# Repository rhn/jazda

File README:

Jazda is a bicycle computer based on AVR microcontrollers and mobile phone screens. The project covers both the software and hardware design, providing the source code and schematics.
Originally, it was built around AtTiny2313, now it's AtMega8. The microcontrollers were chosen because of their popularity and resistance to damage.
The other significant component is the screen. The project aims to be compatible with at least a few popular low-powered displays in the future, but at the moment only one is supported.

Project page:
https://github.com/rhn/jazda
Project wiki:
https://github.com/rhn/jazda/wiki/
Introduction, tutorial and hardware documents:
http://rhn.github.com/jazda/

FEATURES

5 speed measuring functions: current, max, average etc
Cadence measurement
Plotting as you ride
Low power consumption
DIY hardware
Modular code design

ASSEMBLY

For hardware needed to assemble the device, see docs/hardware
The schematics are available in Eagle format in eagle directory AND on the
project page (PNG format).
You will need an AVR programmer to upload the software to the chip!

SOFTWARE BUILDING

Linux:
To build & upload the software, you need:
- avr-gcc
- avr-libc
- avrdude
- Unix shell
1. Connect the AtMega8 chip to your computer using
your programmer (refer to the programmer's manual)
2. Consult avrdude manual to find your programmer's name (in this example, it's
"usbasp")
2. Issue the commands:
cd src
sh ../build.sh usbasp m8 main.c
replacing "usbasp" with your programmer's name

AUTHORS
rhn@porcupinefactory.org

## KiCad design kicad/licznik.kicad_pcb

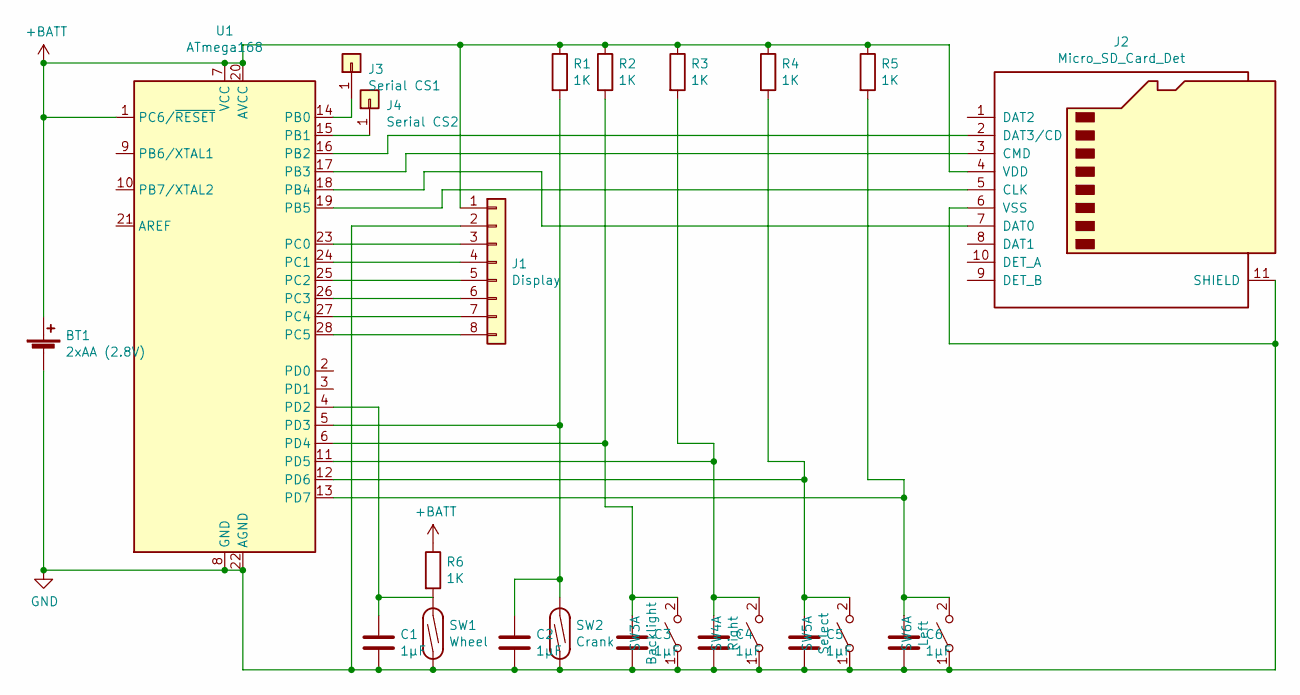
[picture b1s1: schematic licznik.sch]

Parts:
BT1: 2xAA (2.8V); PinHeader_1x02_P2.54mm_Vertical
C1, C2, C3: 1µF; C_0805_2012Metric_Pad1.15x1.40mm_HandSolder
C4, C5, C6: 1µF; C_0805_2012Metric
J1: Display; Nokia screen
J2: Micro_SD_Card_Det; SD_pins
J3: Serial CS1; PinHeader_1x01_P2.54mm_Horizontal
J4: Serial CS2; PinHeader_1x01_P2.54mm_Horizontal
R1, R2, R3, R4, R5, R6: 1K; R_0603_1608Metric
SW1: Wheel; PinHeader_1x02_P2.54mm_Horizontal
SW2: Crank; PinHeader_1x02_P2.54mm_Horizontal
SW3: Backlight; SW_PUSH_6mm_H5mm
SW4: Right; SW_PUSH_6mm_H5mm
SW5: Select; SW_PUSH_6mm_H5mm
SW6: Left; SW_PUSH_6mm_H5mm
U1: ATmega168; DIP-28_W7.62mm

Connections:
+BATT: BT1.1 (+), J1.1, J2.4 (VDD), R1.1, R2.1, R3.1, R4.1, R5.1, R6.1, U1.1 (PC6/~RESET), U1.7 (VCC), U1.20 (AVCC); also elsewhere on the board
GND: BT1.2 (-), C1.2, C2.2, C3.2, C4.2, C5.2, C6.2, J1.2, J2.6 (VSS), J2.11 (SHIELD), SW1.1, SW2.1, SW3.1, SW4.1, SW5.1, SW6.1, U1.8 (GND), U1.22 (AGND); also elsewhere on the board
unnamed: C1.1, R6.2, SW1.2, U1.4 (PD2)
unnamed: C2.1, R1.2, SW2.2, U1.5 (PD3)
unnamed: C3.1, R2.2, SW3.2, U1.6 (PD4)
unnamed: C4.1, R3.2, SW4.2, U1.11 (PD5)
unnamed: C5.1, R4.2, SW5.2, U1.12 (PD6)
unnamed: C6.1, R5.2, SW6.2, U1.13 (PD7)
unnamed: J1.3, U1.23 (PC0)
unnamed: J1.4, U1.24 (PC1)
unnamed: J1.5, U1.25 (PC2)
unnamed: J1.6, U1.26 (PC3)
unnamed: J1.7, U1.27 (PC4)
unnamed: J1.8, U1.28 (PC5)
unnamed: J2.2 (DAT3/CD), U1.16 (PB2)
unnamed: J2.3 (CMD), U1.17 (PB3)
unnamed: J2.5 (CLK), U1.19 (PB5)
unnamed: J2.7 (DAT0), U1.18 (PB4)
unnamed: J3.1, U1.14 (PB0)
unnamed: J4.1, U1.15 (PB1)

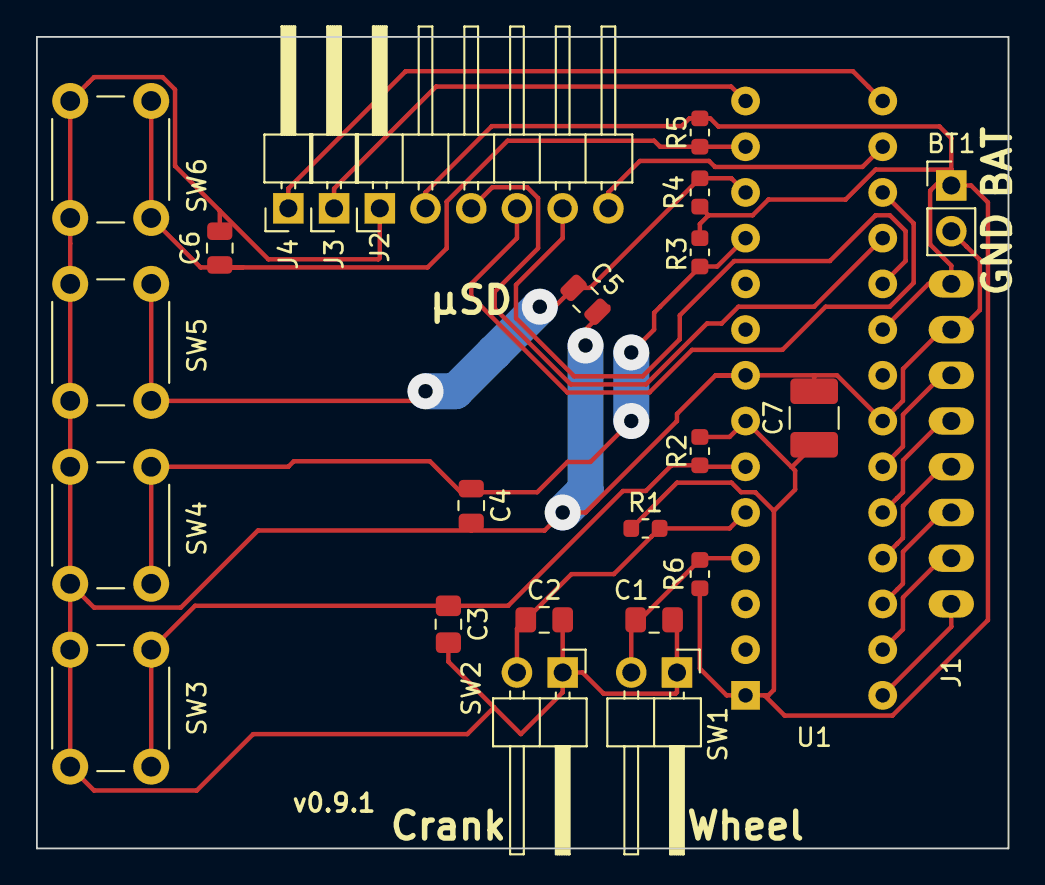
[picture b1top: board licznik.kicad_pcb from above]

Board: 2 copper layers, 54.0 x 45.1 mm, 25 parts (1 on the bottom side), 20 nets.

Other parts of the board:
C7: 100µF; C_1210_3225Metric_Pad1.42x2.65mm_HandSolder

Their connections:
+BATT: C7.1; also elsewhere on the board
GND: C7.2; also elsewhere on the board

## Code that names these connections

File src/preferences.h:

/*
    Copyright 2011 rhn <gihu.rhn@porcupinefactory.org>
    Copyright 2013 Paweł Czaplejewicz

    This file is part of Jazda.

    Jazda is free software: you can redistribute it and/or modify
    it under the terms of the GNU General Public License as published by
    the Free Software Foundation, either version 3 of the License, or
    (at your option) any later version.

    Jazda is distributed in the hope that it will be useful,
    but WITHOUT ANY WARRANTY; without even the implied warranty of
    MERCHANTABILITY or FITNESS FOR A PARTICULAR PURPOSE.  See the
    GNU General Public License for more details.

    You should have received a copy of the GNU General Public License
    along with Jazda.  If not, see <http://www.gnu.org/licenses/>.
*/

/* basic constants and switches, pin defines */

/* REQUIRES: none
*/

// - Inputs

#define PULSEDIR DDRD
#define PULSEPORT PORTD
#define PULSEPIN PD2

#define CRANKDIR DDRD
#define CRANKPORT PIND
#define CRANKPIN PD1

// -- Button interrupt

#define BUTTONDIR DDRD
#define BUTTONPORT PORTD
#define BUTTONPIN PD3

// -- Buttons

#define LEFTPIN PD7
#define LEFTPORT PIND
#define LEFTDIR DDRD

#define RIGHTPIN PD0
#define RIGHTPORT PIND
#define RIGHTDIR DDRD

#define SELECTPIN PD6
#define SELECTPORT PIND
#define SELECTDIR DDRD

#define BACKLIGHTBTNPIN PD4
#define BACKLIGHTBTNPORT PIND
#define BACKLIGHTBTNDIR DDRD

// - Output
// -- Screen

#define CLKDIR DDRC
#define CLKPORT PORTC
#define CLKPIN PC4

#define SDADIR DDRC
#define SDAPORT PORTC
#define SDAPIN PC3

#define D_CDIR DDRC
#define D_CPORT PORTC
#define D_CPIN PC2

#define SCEDIR DDRC
#define SCEPORT PORTC
#define SCEPIN PC0
   
#define RSTDIR DDRC
#define RSTPORT PORTC
#define RSTPIN PC1

// -- Backlight
#define BACKLIGHTDIR DDRC
#define BACKLIGHTPORT PORTC
#define BACKLIGHTPIN PC5

/* special options */
#define HIGH_PRECISION_CALCULATIONS // makes speed calculation 32-bit instead of truncating to 16
#define LONG_CALCULATIONS // makes calculations possible on longer data types
#define FRAC_BITS 10 // Fixed-point fraction for PULSE_DIST and SPEED_FACTOR. WARNING! modifying may lead to overflow errors and better precision (most likely just the former). Less then 8 is not recommended if LONG_SPEED is used
#define ONE_SECOND 3695 // in timer ticks, calibrated for 1MHz/256 // TODO: autocalculate

/* PREFERENCES */
// #define DEBUG

#define CRANK
#define CADENCE
#define STORAGE
#define BACKLIGHT
#define DISTANCE
#define CURRENT_SPEED
#define SPEED_VS_DISTANCE_PLOT
#define STOPWATCH
#define MAXSPEED
#define AVGSPEED
#define COMBINED_RESET
#define SPEED_VS_TIME_PLOT
#define CONFIG
// #define MOD_BACKLIGHT // backlight control via module
#define BACKLIGHT_BUTTON // backlight control via hw button
//#define BACKLIGHT_VOLTAGE // shows voltage along with backlight
#define LCD_CLEAN


#define METRIC_PULSE_DIST 2133L // millimeters

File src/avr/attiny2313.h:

/*
    Copyright 2011 rhn <gihu.rhn@porcupinefactory.org>

    This file is part of Jazda.

    Jazda is free software: you can redistribute it and/or modify
    it under the terms of the GNU General Public License as published by
    the Free Software Foundation, either version 3 of the License, or
    (at your option) any later version.

    Jazda is distributed in the hope that it will be useful,
    but WITHOUT ANY WARRANTY; without even the implied warranty of
    MERCHANTABILITY or FITNESS FOR A PARTICULAR PURPOSE.  See the
    GNU General Public License for more details.

    You should have received a copy of the GNU General Public License
    along with Jazda.  If not, see <http://www.gnu.org/licenses/>.
*/

#define CLKDIR DDRB
#define CLKPORT PORTB
#define CLKPIN PB1

#define RSTDIR DDRB
#define RSTPORT PORTB
#define RSTPIN PB2

#define SCEDIR DDRB
#define SCEPORT PORTB
#define SCEPIN PB3

#define SDADIR DDRB
#define SDAPORT PORTB
#define SDAPIN PB4

#define D_CDIR DDRB
#define D_CPORT PORTB
#define D_CPIN PB5

#include "avr.h"

void setup_cpu(void) {
// makes CPU run at 1 MHz
// clock prescaler, device clock must be 8 MHz
  clock_prescale_set(clock_div_8);
}

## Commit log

2010-08-11 Added schematic
2010-08-14 added readme
2010-08-14 added glyph_info structure, compiles for atmega8
2010-08-14 removed glyph_info references to observe a massive size decrease
2010-08-14 resolved some #define preferences mess, splt device-specific functions into separate files
2010-08-15 set default ports for each chip independently, works on atmega8
2010-08-15 adjusted default pinout to my likings
2010-08-16 some define adjustments
2010-08-16 numbers have set width now
2010-08-16 added broken speed vs distance plot
2010-08-16 finished speed vs distance plot
2010-08-16 added TODOs
2010-08-16 fixed stop speed decrease
2010-08-16 removed debugging code
2010-08-19 added a screen failure detection section
2010-08-22 fixed screen failure mode
2010-08-25 pushed some avr-specific functions to /avr
2010-08-25 split drawing and screen support
2010-08-25 moved interrupts away to avr.h
2011-02-20 builds for atmega8
2011-02-20 added examples
2011-04-10 lcd example and troubleshooting
2011-04-12 interrupt emulator works
2011-04-12 added missing files
2011-04-13 added drawing example, fixed drawing glitch
2011-04-13 minor fixes
2011-06-18 altered examples to mirror board, made main project compile
2011-06-18 moved speed to builtins
2011-06-19 fixed overflow in speed calculation, added comments
2011-06-19 fixed constant calculation
2011-06-19 moved distance to modules, sketched modules API
2011-06-19 fixed debug print
2011-06-19 added missing files, dummy module, first working version of modules
2011-06-20 extended module sketch
2011-06-21 failed attempt at modules
2011-06-21 added event counter
2011-06-21 fixed module selection
2011-06-21 module and emuint systems working
2011-06-22 added module logos, moved svdplot to a module
2011-06-22 made svdplot work
2011-06-22 fixed svdplot
2011-06-23 improved module redrawing
2011-06-23 introduced extended timer
2011-06-23 added on_each_second timer and a stopwatch
2011-06-23 added broken maxspeed module
2011-06-23 fixed and reworked maxspeed
2011-06-24 added average speed module w/o icon and improved speed calculation over long distances
2011-06-24 added stopwatch pausing, fixed speed timeouts
2011-06-24 improved average calculation
2011-06-25 fixed avgspeed calculation
2011-06-25 moved some module references to modules/baseh.h
2011-06-25 ordered modules/base.h
2011-06-25 combined reset
2011-06-25 misc
2011-06-25 made plot support separate from any module
2011-06-26 fixed separate plot module, overall size increased by 68B, while it could have optimized out to 0...
2011-06-26 added undebugged speed vs time plot
2011-06-26 fixed plot display, svtplot calculations
2011-06-26 increased timer resolution
2011-06-26 calibrated for 1MHz internal clock@2.4V
2011-06-26 added shorthand null on_select function
2011-06-26 fixed overflow warning
2011-06-26 module clearscreen is global now
2011-06-26 untested attempt at ordering code
2011-06-26 fixed again
2011-06-26 a small step towards ordered code
2011-06-26 disentangled timers with help of a dummy module
2011-06-26 github generated gh-pages branch
2011-06-27 fixed redrawing
2011-06-27 added space after a stop
2011-06-27 fixed race condition in module redraw
2011-06-27 added module flags and optimized redrawing
2011-06-27 added missing volatile keyword
2011-06-27 dropped default bitfields in favor of full-bte flags to save ROM at expense of RAM
2011-06-27 fixed (harmless) race condition in speed display
2011-06-27 removed workaround
2011-06-27 powersave: speed refresh only on update now
2011-06-28 added media files
2011-06-28 added cost breakdown and modified front page
2011-06-28 lotsa stuff
2011-06-28 added schematics
2011-06-29 added licensing information
2011-06-29 added frontpage image
2011-06-29 added quick start to readme
2011-06-29 renamed code files from .h to .c
2011-07-06 separated generic calculations from speed
2011-07-06 moved emuint to avr, renamed functions, started making code linker-friendly, added license notices. UNTESTED
2011-07-09 added crank builtin, added some header files
2011-07-23 updated examples & preferences to be compatible with prototype
2011-07-25 properly added cadence module
2011-07-25 improved some names
2011-07-25 improved some more names
2011-07-27 wrote a proper timer module
2011-07-27 fixed speed damping
2011-07-27 really fixed speed reducing and separated fake speed reading from real ones
2011-07-27 updated maxspeed to separated speed data
2011-07-27 added missing header
2011-07-27 moved timer to lib
2011-07-27 moved speed pulse functions to signal
2011-07-27 started separating basic speed/wheel functions
2011-07-28 untested - separated wheel and speed code
2011-07-30 broken timer in need of a rewrite
2011-07-30 rewritten timer to a naive but working implementation
2011-07-30 split speed and wheel into separate files
2011-07-30 added drawing.h and updated some header references
2011-07-30 rearranged some declarations and includes
2011-07-30 made stopwatch start immediately
2011-07-31 fixed a situation with many timers set to the same instant
2011-07-31 promoted cadence to a builtin
2011-07-31 added cadence bar
2011-07-31 added crank stop event
2011-08-04 allowed speed_factor to become variable
2011-08-04 allowed pulse_dist to become variable
2011-08-04 fixed typo
2011-08-05 config module works
2011-08-05 fixed pulse_dist updating
2011-08-05 fixed speed_factor updating
2011-08-05 moved plots to /lib
2011-08-05 added a missing file
2011-08-05 added missing includes for plots.h
2011-08-05 moved modules to /lib
2011-08-05 added some references to lib/modules
2011-08-06 moved signals to /
2011-08-06 cleaned up common.h
2011-08-06 removed obsolete values.h
2011-08-06 added screeb header file
2011-08-20 added noop
2011-08-20 resized shown values range, added missing includes
2011-08-20 removed commented code
2011-08-20 now BACKLIGHT preference enables backlight module
2011-08-20 added F_CPU note to docs
2011-08-20 exposed SPEED_DIGITS, fixed some #includes, added decimal points to each number with one
2011-08-20 moved wheel and crank to /sensors
2011-08-20 added proper avgspeed symbol
2011-08-22 fixed display bug in cadence builtin
2011-08-22 improved examples, made sure they build
2011-08-22 added eagle board and schematic files
2011-08-22 updated docs
2011-08-31 updated text
2011-09-01 added v1 photos and module icons
2011-09-01 updated hardware design
2011-09-01 updated board design
2011-09-01 added pcb
2011-09-23 added links to the front page
2012-02-19 added solderpad directory
2012-06-14 added a preliminary mmc example and a scons build file
2013-02-10 fixed examples buildability
2013-02-10 added missing config module
2013-02-14 added lcd_clean function
2013-02-14 made use of lcd_clean function
2013-02-14 added ADC support with an example
2013-02-14 added battery status monitor
2013-02-14 reducing power usage at the cost of a small delay - turning on ADC for each battery reading
2013-02-15 added modules readme and voltage display
2013-02-15 removed misleading line from example docs
2013-04-06 added storage subsystem
2013-04-07 some variables cleanup
2013-04-21 backlight promoted to its own section, refactored constants, button-backlight added
2013-05-02 added number printing test case
2013-05-02 separated bcd handling outside of drawing function
2013-05-02 pushed bcd farther
2013-05-02 optimizations
2013-05-02 cleaned up number printing
2013-05-02 moved bcd functions to a separate file
2013-05-02 Moved glyphs to header
2013-05-02 switched glyphs to using glyph_point_t
2013-05-02 cleanup in glyph display
2017-02-07 Added new index from .md file
2017-02-07 Fixed index formatting
2017-02-07 Added contact info and images
2017-02-07 Fixed picutre
2017-02-07 Added size restriction on image
2017-02-07 Better contact info
2018-11-19 Add crank pull up resistor
2018-11-19 Dimensions trim, reroute edy trace
2018-11-23 Added elements for accelerometers, updated Nokia screen, shrunk the board
2018-11-23 Moved buttons closer to the middle
2018-11-23 Spaced around components for easy soldering
2018-11-23 Added screen mounting holes
2018-11-23 Added logo
2018-11-23 Added silkscreen logos, placed silkscreen properly
2018-11-23 Fix track moving over a hole
2018-11-23 Marked version 0.9.1
2018-11-30 Added more files just in case...
2018-11-30 Moved files to kicad/
2018-11-30 Removed Eagle board
2018-12-23 Allowed kicad to fix missing libraries
2018-12-23 PCB footprint: Set screen holes to 1mm
2018-12-23 PCB: Adjust position of screen mounting holes
2018-12-23 PCB: Fix screen hole placement, reduce board size
2018-12-23 PCB: Stick out the IO header
2018-12-23 PCB: Move holes description away from polluting the board
2018-12-23 PCB: Use optional RTC capacitor
2018-12-23 Schematic: Added comments
